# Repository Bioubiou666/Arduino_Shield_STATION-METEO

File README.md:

# Arduino_Shield_STATION-METEO
Shield pour Arduino UNO/Elegoo UNO, projet de station météo avec comme composants : pin, pin, pin, support LCD, WC1602A (écran LCD 16x2 Alphanumeric , 8 bit parallel bus, 5V VDD), DHT11, potentiomêtre.

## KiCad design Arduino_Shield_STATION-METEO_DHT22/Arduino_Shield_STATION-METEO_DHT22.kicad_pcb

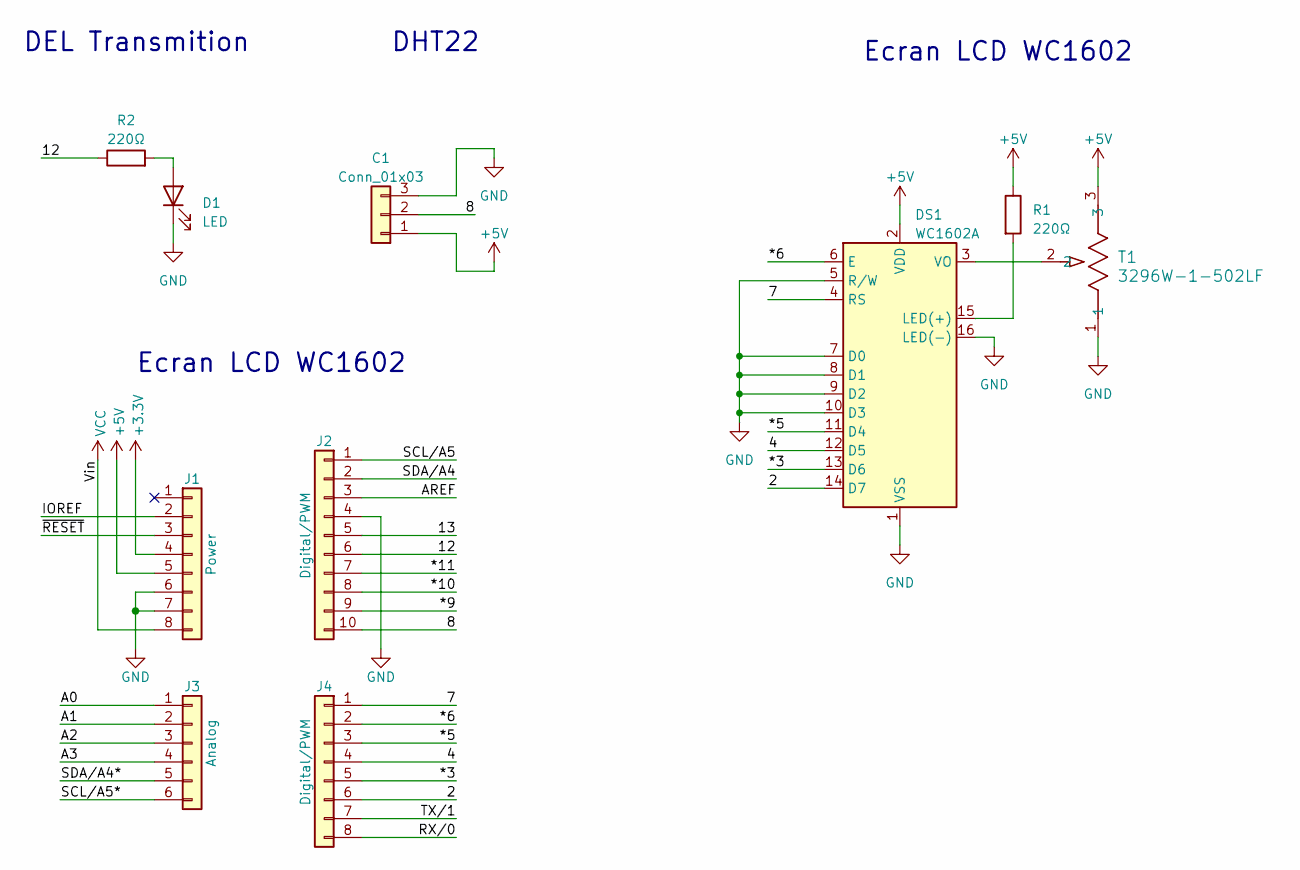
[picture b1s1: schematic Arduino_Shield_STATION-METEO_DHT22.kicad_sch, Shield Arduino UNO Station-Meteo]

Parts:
C1: Conn_01x03; JST_EH_B3B-EH-A_1x03_P2.50mm_Vertical
D1: LED; LED_D3.0mm
DS1: WC1602A
J1: Power; PinSocket_1x08_P2.54mm_Vertical
J2: Digital/PWM; PinSocket_1x10_P2.54mm_Vertical
J3: Analog; PinSocket_1x06_P2.54mm_Vertical
J4: Digital/PWM; PinSocket_1x08_P2.54mm_Vertical
R1, R2: 220Ω; R_Axial_DIN0207_L6.3mm_D2.5mm_P15.24mm_Horizontal
T1: 3296W-1-502LF; POT_3296W

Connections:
+3V3: J1.4
+5V: C1.1, DS1.2 (VDD), J1.5, R1.1, T1.3
/2: DS1.14 (D7), J4.6
/4: DS1.12 (D5), J4.4
/7: DS1.4 (RS), J4.1
/8: C1.2, J2.10
/12: J2.6, R2.1
/13: J2.5
/*3: DS1.13 (D6), J4.5
/*5: DS1.11 (D4), J4.3
/*6: DS1.6 (E), J4.2
/*9: J2.9
/*10: J2.8
/*11: J2.7
/A0: J3.1
/A1: J3.2
/A2: J3.3
/A3: J3.4
/AREF: J2.3
/IOREF: J1.2
/RX/0: J4.8
/SCL/A5: J2.1
/SCL/A5*: J3.6
/SDA/A4: J2.2
/SDA/A4*: J3.5
/TX/1: J4.7
/~RESET: J1.3
GND: C1.3, D1.1 (K), DS1.1 (VSS), DS1.5 (R/W), DS1.7 (D0), DS1.8 (D1), DS1.9 (D2), DS1.10 (D3), DS1.16 (LED(-)), J1.6, J1.7, J2.4, T1.1
unnamed: D1.2 (A), R2.2
unnamed: DS1.15 (LED(+)), R1.2
unnamed: DS1.3 (VO), T1.2
VCC: J1.8

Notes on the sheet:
DEL Transmition
Ecran LCD WC1602
DHT22

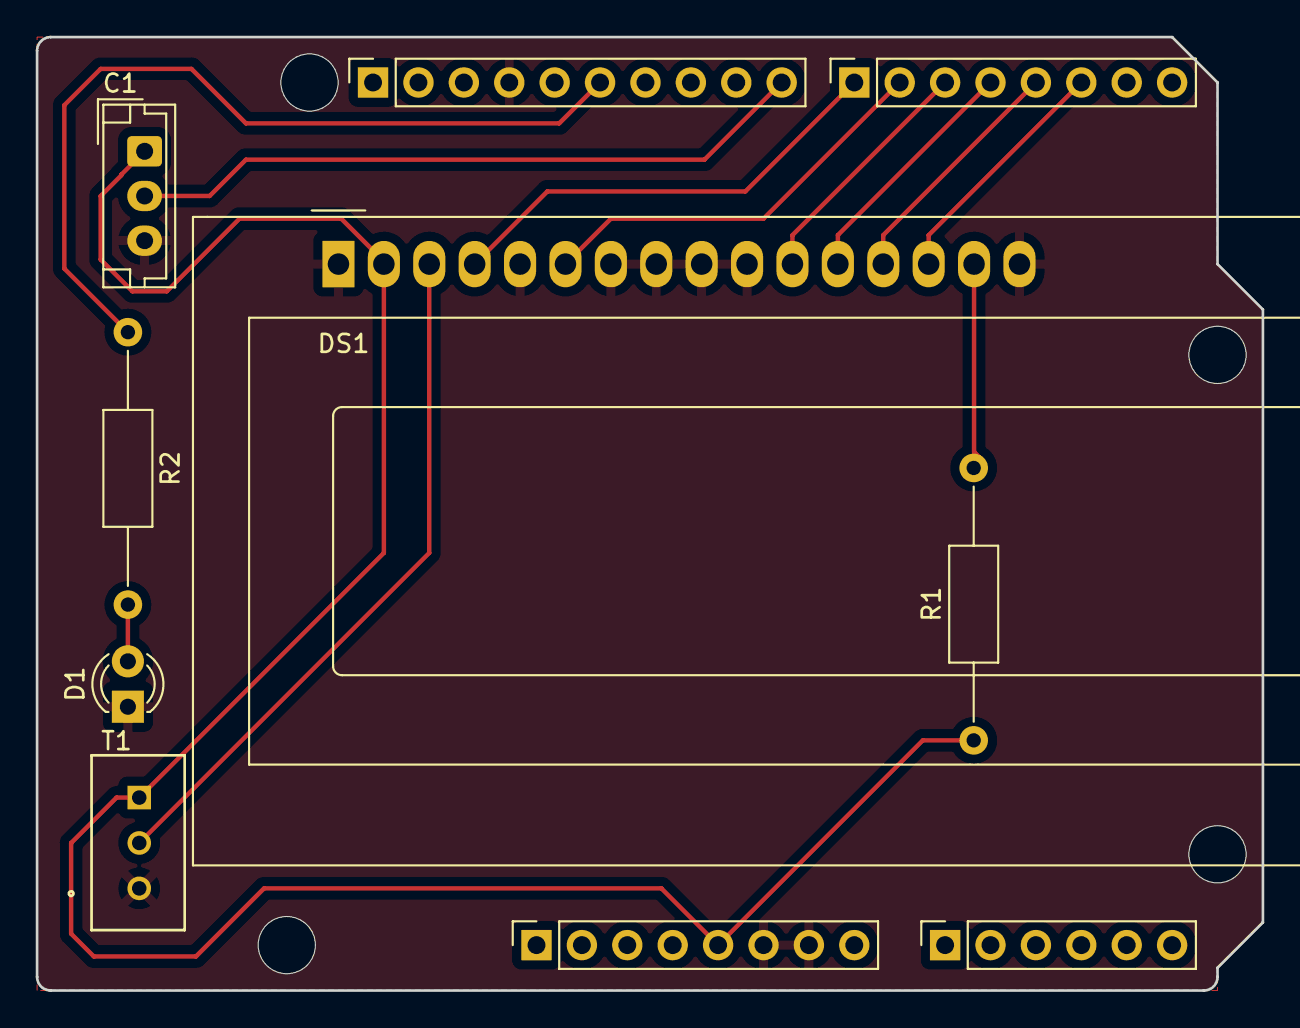
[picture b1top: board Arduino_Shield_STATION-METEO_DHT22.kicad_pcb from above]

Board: 2 copper layers, 68.6 x 53.3 mm, 14 parts (0 on the bottom side), 13 nets.

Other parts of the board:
MH1, MH2, MH3, MH4: MountingHole_3.2mm

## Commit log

2023-06-19 Circuit imprimmé : #V1# KiCad fichier shield arduino pour DHT11 + KiCad fichier shield arduino pour DHT22
